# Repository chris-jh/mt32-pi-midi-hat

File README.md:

# mt32-pi-midi-hat
A Raspberry Pi Midi Hat for the project mt32-pi by Dale Whinham (https://github.com/dwhinham/mt32-pi).

This PCB is designed from the schematic available from the above project.

The Gerbers have been created from the recommendations at JLCPCB.

(https://support.jlcpcb.com/article/102-kicad-515---generating-gerber-and-drill-files)

You may need to re-generate for your chosen PCB Manufacturer

Version 1.7.2 Copyright 2021 Chrissy

* Moved a trace that was too close to the mounting screw hole. Could cause a short if over tighten to expose the trace. (see https://github.com/chris-jh/mt32-pi-midi-hat/issues/3)

Version 1.7.1 Copyright 2021 Chrissy

* Moved the Midi-Din slightly

Version 1.7 Copyright 2021 Chrissy

* Fixed Silk Screen error on buttons for mt32/sf and Synth, they were opposite

Version 1.6 Copyright 2021 Chrissy

* Removed Hitachi HD44780 4 bit connection, use i2c version
* Added control pins and buttons, see (https://github.com/dwhinham/mt32-pi/wiki/Control-surface)

## Audio DAC's

I designed this Hat to accommodate 2 different PCM5102 DAC boards that are available from Amazon or eBay.

***GY-PCM5102***

***CJMCU-5102***

Currently the GY-PCM5102 version seems to be the most popular on Amazon and eBay, just search for PCM5102.

## Screen's

**SSD1306 OLED**

The Hat can take either the 128x32 SSD1306 OLED, or the 128x64 SSD1306 OLED

***SSD1306 OLED 128x32***

***SSD1306 OLED 128x64***

Again both screens are available from Amazon or eBay.

The 128x64 OLED connects on the board at this position here.

You will need to put some none conductive material under the OLED,<br>so it does not short agains the Pins of the Raspberry Pi.

When you buy your screen, make sure the PIN order is as follow's (left to right, looking down on the screen):-

| 1 | 2 | 3 | 4 |
|---|---|---|---|
|GND|VCC|SCL|SDA|

You can see this in the photo above.

Some SSD1306 OLED's have Pins 1 and 2 swapped, which will be bad. So please double check.

***Hitachi HD44780***

There are two versions of this screen, one that communicates via the i2c (like the above OLEDS) or a direct connection.

I have removed the direction connection from v1.6 to give enough room to fit the control buttons.

Use the i2c version only and you will need to connect the screen to one of the OLED connections J2 or J3 on the PCB.

The Hitachi screen can also come in different sizes, ideally you want one that is 20 characters in length and either 2 or 4 lines.

<br>

### Configuration

Please see the main mt32-pi Project (https://github.com/dwhinham/mt32-pi) on how to configure and use your screen and DAC.

### BOM

| Reference | Value | Quantity | URL |
|-----------|-------|----------|-----|
| C1        | 100nf | 1        | https://www.mouser.co.uk/ProductDetail/Murata-Electronics/RCER71E104K0K1H03B?qs=Ey7%2FXF42M3ci4g3t0g7SIw%3D%3D |
| R1        | 220Ω | 1        | https://www.mouser.co.uk/ProductDetail/Vishay-Beyschlag/MBB02070C2200FCT00?qs=PwR17mNzlcOWyOoLtTQfsw%3D%3D |
| R2        | 1KΩ 5% | 1        | https://www.mouser.co.uk/ProductDetail/Vishay-Dale/CCF071K00JKE36?qs=NQWA6AwZmkMdaaeOGvuguw%3D%3D |
| D1        | 1N4148 | 1        | https://www.mouser.co.uk/ProductDetail/ON-Semiconductor-Fairchild/1N4148?qs=i4Fj9T%2FoRm8RMUhj5DeFQg%3D%3D    |
| U1        | H11L1 | 1        | https://www.mouser.co.uk/ProductDetail/ON-Semiconductor-Fairchild/H11L1M?qs=P36CEcFBmYxn5ViwkIckpw%3D%3D |
| J1        | DIN-5 | 1        | https://www.mouser.co.uk/ProductDetail/490-SDS-50J |
| J2 or J3    | SSD1306 OLED | 1        | Amazon or eBay |
| J4 or J5    | DAC GY-PCM5102<br>or<br>CJMCU-5102  | 1        | Amazon or eBay |
| J6    | External Button Pin Header 1x6 | 1        | Amazon or eBay |
| SW1,2,3,4 | Tact Switch 6x6mm | 4      | Amazon or eBay |
| Pi        | Header| 1 | https://www.mouser.co.uk/ProductDetail/Samtec/SSQ-120-23-G-D?qs=rU5fayqh%252BE1BMVd%252BDZONqg%3D%3D |

You may want to get some general Pin Headers 2.54mm, only 1 extra pin is used to stabilise the DAC's for when pushing in the headphone jack.

[**THT Interactive BOM**][IBOMTHT1_6]

## !!!!! WARNING !!!!!

Use at your own risk. I accept no responsibility if this damages any of your equipment.

[IBOMTHT1_6]: http://htmlpreview.github.io/?https://raw.githubusercontent.com/chris-jh/mt32-pi-midi-hat/main/bom/mt32-pi-midi-hat_bom_v1_6.html

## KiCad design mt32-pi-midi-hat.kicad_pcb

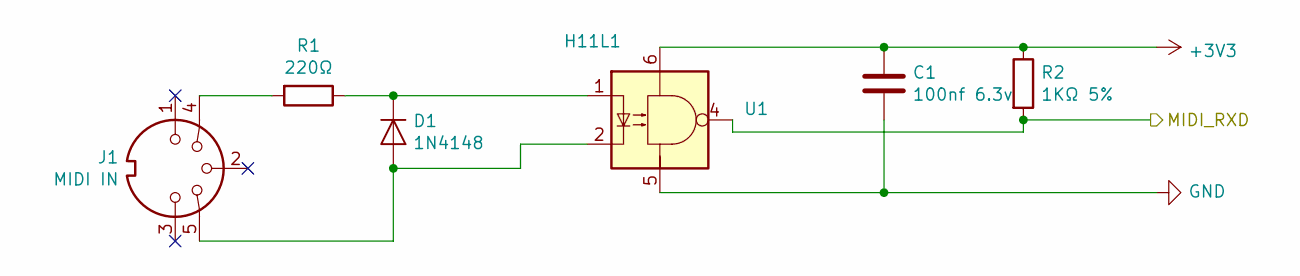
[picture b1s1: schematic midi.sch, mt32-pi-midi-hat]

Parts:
C1: 100nf 6.3v; C_Disc_D7.0mm_W2.5mm_P5.00mm
D1: 1N4148; D_DO-35_SOD27_P10.16mm_Horizontal
J1: MIDI IN; DIN-5-Variable
R1: 220Ω; R_Axial_DIN0207_L6.3mm_D2.5mm_P10.16mm_Horizontal
R2: 1KΩ 5%; R_Axial_DIN0207_L6.3mm_D2.5mm_P10.16mm_Horizontal
U1: H11L1; DIP-6_W7.62mm

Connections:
+3V3: C1.1, R2.1, U1.6; also elsewhere on the board
/Midi/MIDI_RXD: R2.2, U1.4; also elsewhere on the board
GND: C1.2, U1.5; also elsewhere on the board
unnamed: D1.1 (K), R1.1, U1.1
unnamed: D1.2 (A), J1.5, U1.2
unnamed: J1.4, R1.2

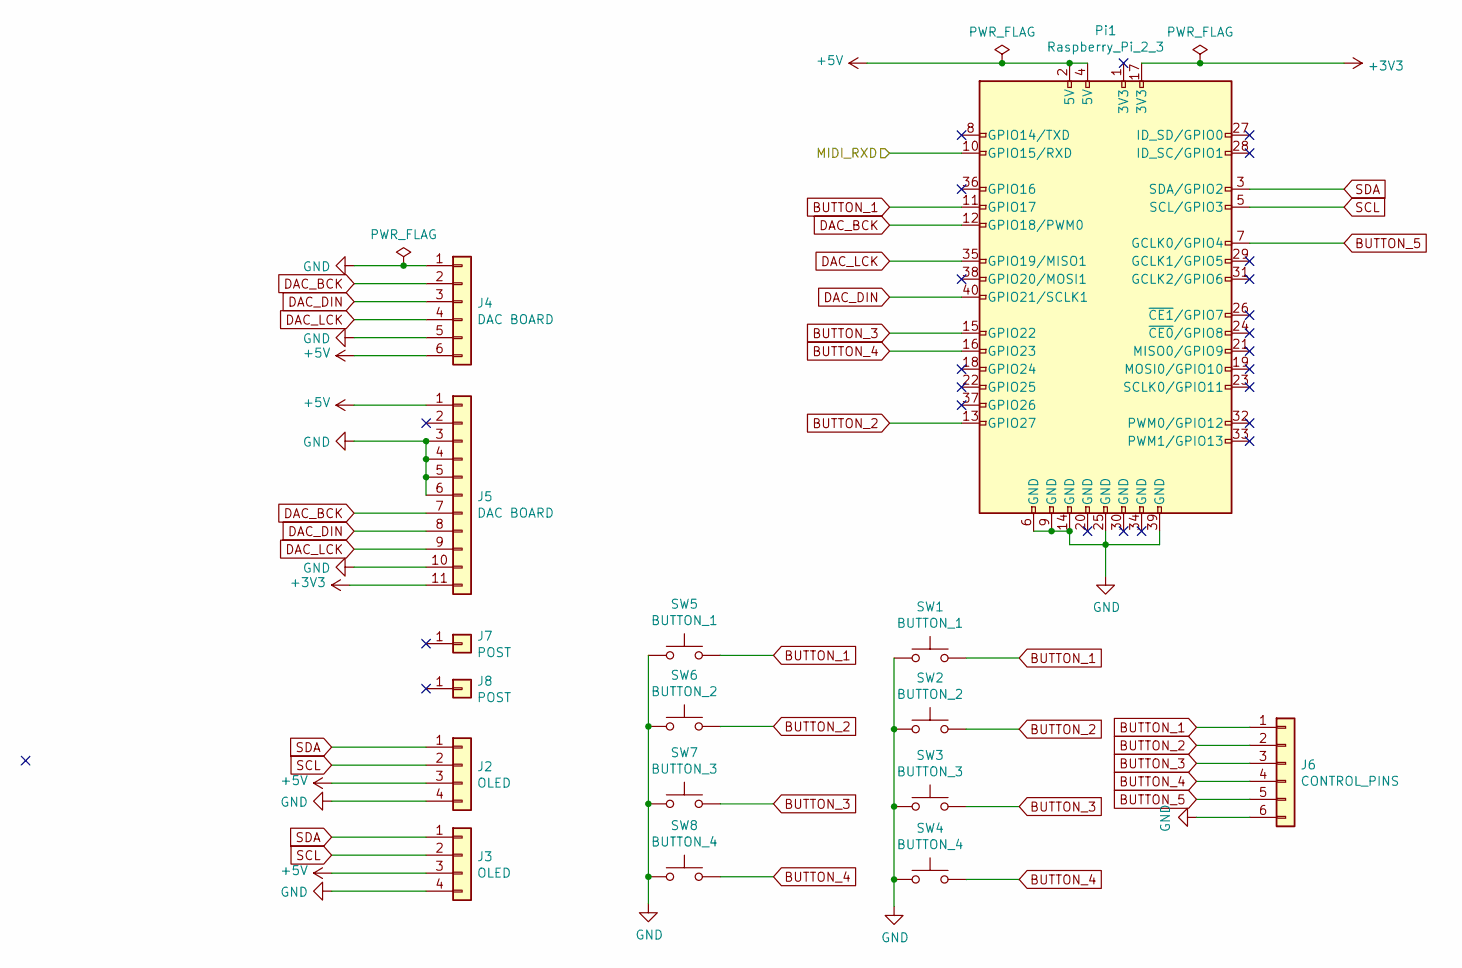
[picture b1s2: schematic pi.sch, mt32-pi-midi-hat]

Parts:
J2, J3: OLED; PinHeader_1x04_P2.54mm_Vertical
J4: DAC BOARD; PinHeader_1x06_P2.54mm_Vertical
J5: DAC BOARD; PinHeader_1x11_P2.54mm_Vertical
J6: CONTROL_PINS; PinHeader_1x06_P2.54mm_Vertical
J7, J8: POST; PinHeader_1x01_P2.54mm_Vertical
Pi1: Raspberry_Pi_2_3; raspberrypi_2_3
SW1, SW5: BUTTON_1; SW_PUSH_6mm_SLIM
SW2, SW6: BUTTON_2; SW_PUSH_6mm_SLIM
SW3, SW7: BUTTON_3; SW_PUSH_6mm_SLIM
SW4, SW8: BUTTON_4; SW_PUSH_6mm_SLIM

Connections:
+3V3: J5.11, Pi1.17 (3V3); also elsewhere on the board
+5V: J2.3, J3.3, J4.6, J5.1, Pi1.2 (5V), Pi1.4 (5V)
/Midi/MIDI_RXD: Pi1.10 (GPIO15/RXD); also elsewhere on the board
BUTTON_1: J6.1, Pi1.11 (GPIO17), SW1.2, SW5.2
BUTTON_2: J6.2, Pi1.13 (GPIO27), SW2.2, SW6.2
BUTTON_3: J6.3, Pi1.15 (GPIO22), SW3.2, SW7.2
BUTTON_4: J6.4, Pi1.16 (GPIO23), SW4.2, SW8.2
BUTTON_5: J6.5, Pi1.7 (GCLK0/GPIO4)
DAC_BCK: J4.2, J5.7, Pi1.12 (GPIO18/PWM0)
DAC_DIN: J4.3, J5.8, Pi1.40 (GPIO21/SCLK1)
DAC_LCK: J4.4, J5.9, Pi1.35 (GPIO19/MISO1)
GND: J2.4, J3.4, J4.1, J4.5, J5.3, J5.4, J5.5, J5.6, J5.10, J6.6, Pi1.6 (GND), Pi1.9 (GND), Pi1.14 (GND), Pi1.25 (GND), Pi1.39 (GND), SW1.1, SW2.1, SW3.1, SW4.1, SW5.1, SW6.1, SW7.1, SW8.1; also elsewhere on the board
SCL: J2.2, J3.2, Pi1.5 (SCL/GPIO3)
SDA: J2.1, J3.1, Pi1.3 (SDA/GPIO2)

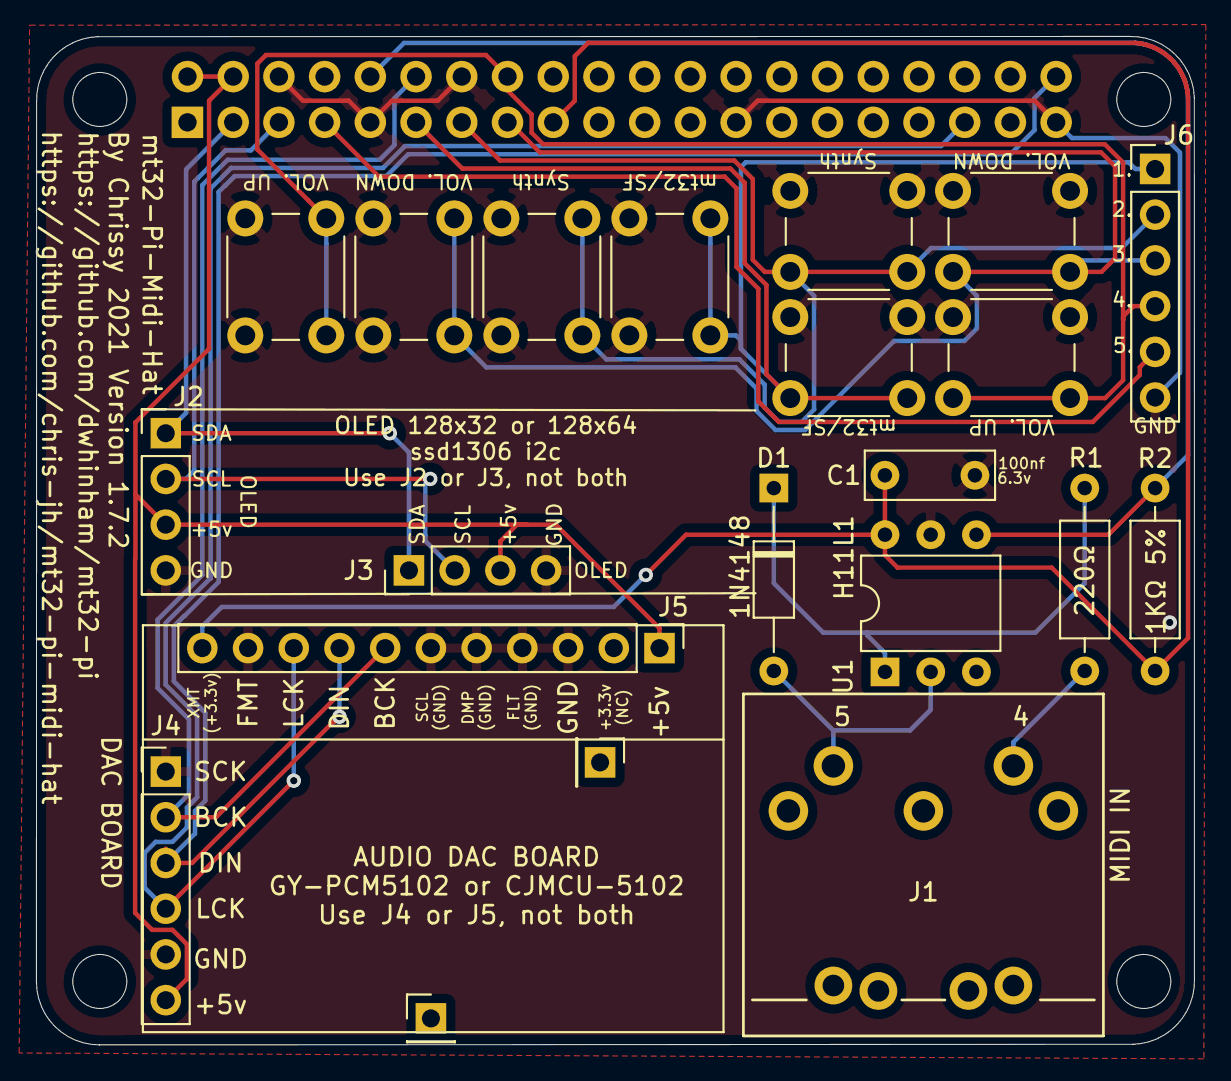
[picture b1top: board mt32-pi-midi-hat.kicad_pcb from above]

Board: 2 copper layers, 64.3 x 56.0 mm, 22 parts (0 on the bottom side), 17 nets.

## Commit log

2020-12-05 mt32-pi-midi-hat
    First commit
2020-12-05 Update README.md
    Fix path error
2020-12-05 Update README.md
    Added Pi Header
2020-12-05 Update README.md
    Added more information about the HD44780 screen
2020-12-05 Update README.md
    Extra note on BOM
2020-12-05 Update README.md
    Added damage disclaimer
2020-12-05 Update README.md
    Updated SSD1306 Oled Pin 1 and 2 swap note
2020-12-09 Update README.md
    Wrong Pin Header, updated to correct one
2021-01-03 Version 1.6
    1. Removed Hitachi 4bit version
    2. Added new buttons from version 0.8 of the mt32-pi project
2021-01-03 fix wrong date on back
    fixed wrong version and date on back of pcb
    slight adjustment of 128x64 oled pins
2021-01-16 Version 1.7
    Fixed Silk Screen error for buttons mt32/SF and Synth
2021-01-16 Update README.md
    added tact switch to bom list
2021-02-05 Update README.md
    Update about gerbers
2021-02-05 Update README.md
    Moved gerber info
2021-02-18 V1.7.1
    Moved the Midi Din Slightly, may have caused issues with OSHPark.
2021-06-13 Update README.md
    fixed typo
2021-06-13 Version 1.7.2
    moved a trace too near the mounting screw hole
